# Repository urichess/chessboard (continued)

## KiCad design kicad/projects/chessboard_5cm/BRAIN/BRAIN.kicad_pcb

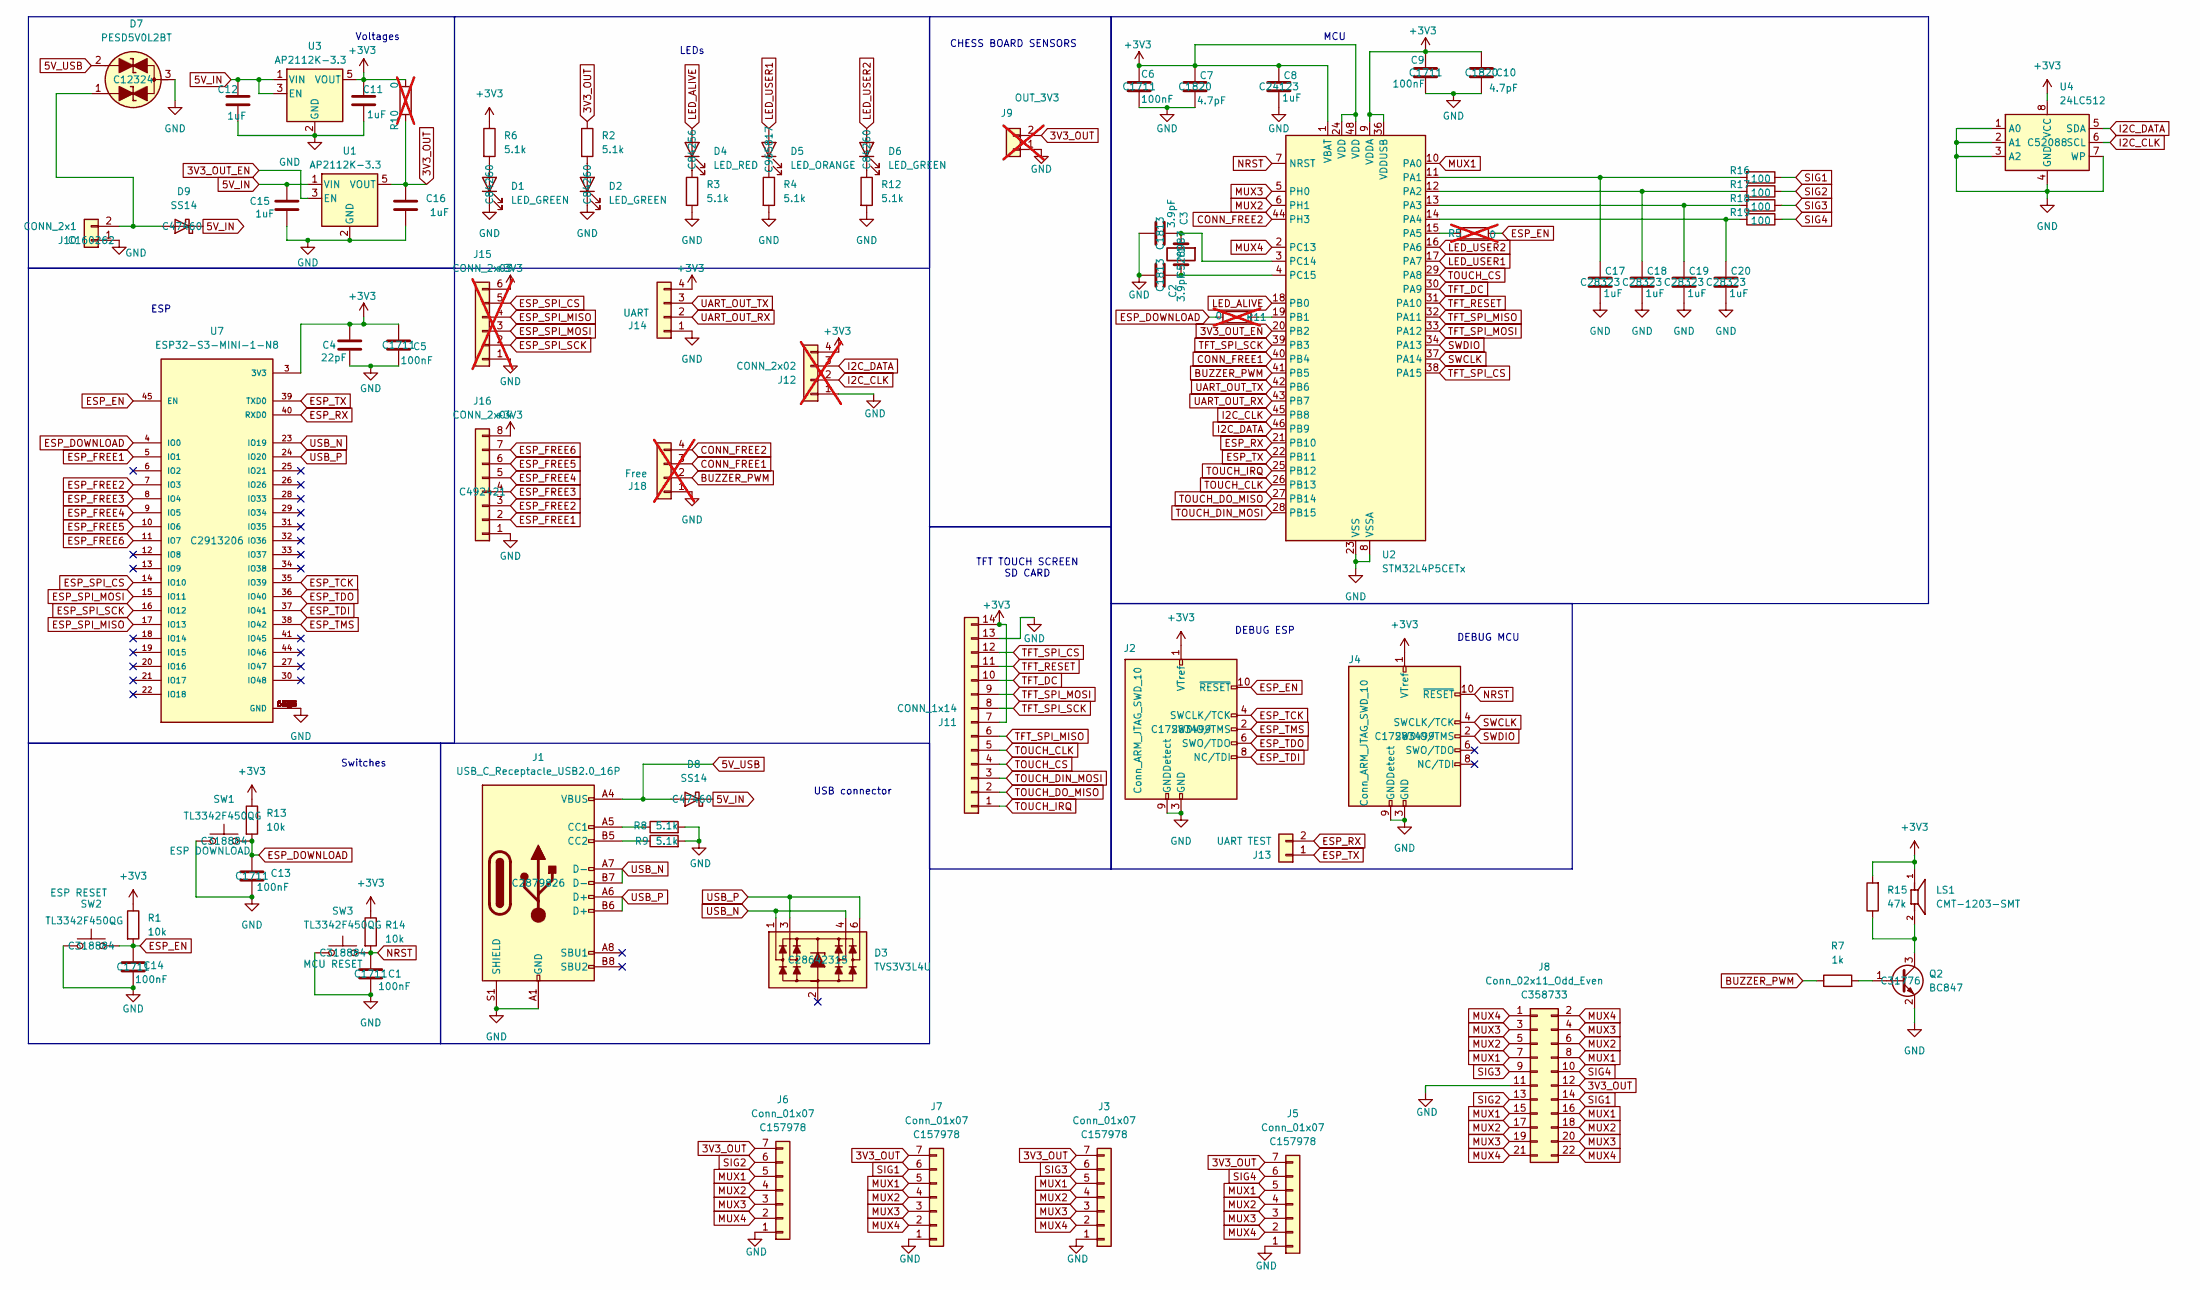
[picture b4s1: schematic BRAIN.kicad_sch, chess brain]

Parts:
C1, C5, C6, C9, C13, C14: 100nF; C_0805_2012Metric_Pad1.18x1.45mm_HandSolder; LCSC p/n C1711
C2, C3: 3.9pF; C_0805_2012Metric_Pad1.18x1.45mm_HandSolder; LCSC p/n C1813
C4: 22pF; C_0805_2012Metric_Pad1.18x1.45mm_HandSolder; LCSC p/n C1804
C7, C10: 4.7pF; C_0805_2012Metric_Pad1.18x1.45mm_HandSolder; LCSC p/n C1820
C8, C11, C12, C15, C16: 1uF; C_0805_2012Metric_Pad1.18x1.45mm_HandSolder; LCSC p/n C24123
C17, C18, C19, C20: 1uF; C_0805_2012Metric_Pad1.18x1.45mm_HandSolder; LCSC p/n C28323
D1, D2, D6: LED_GREEN; LED_0805_2012Metric_Pad1.15x1.40mm_HandSolder; LCSC p/n C84260
D3: TVS3V3L4U; TSOP-6_1.65x3.05mm_P0.95mm; LCSC p/n C28642315
D4: LED_RED; LED_0805_2012Metric_Pad1.15x1.40mm_HandSolder; LCSC p/n C84256
D5: LED_ORANGE; LED_0805_2012Metric_Pad1.15x1.40mm_HandSolder; LCSC p/n C965817
D7: PESD5V0L2BT; SOT-23; LCSC p/n C12324
D8, D9: SS14; D_SMA; LCSC p/n C47460
J1: USB_C_Receptacle_USB2.0_16P; USB_C_Receptacle_GCT_USB4105-xx-A_16P_TopMnt_Horizontal_Mod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; LCSC p/n C2879826
J2, J4: Conn_ARM_JTAG_SWD_10; GCT_BD125-10-A-0305-0580-L-B; LCSC p/n C17283499
J3, J5, J6, J7: Conn_01x07; JST_B7B-ZR_LF__SN_; LCSC p/n C157978
J8: Conn_02x11_Odd_Even; PinSocket_2x11_P2.54mm_Vertical; LCSC p/n C358733
J9: CONN_01x02; PinSocket_1x02_P2.54mm_Vertical; LCSC p/n C2935896; not fitted
J10: CONN_2x1; JST_EH_B2B-EH-A_1x02_P2.50mm_Vertical; LCSC p/n C160262
J11: CONN_1x14; PinSocket_1x14_P2.54mm_Vertical; LCSC p/n C2883731
J12: CONN_2x02; PinHeader_2x02_P2.54mm_Vertical; LCSC p/n C160338; not fitted
J13: UART TEST; PinHeader_1x02_P2.54mm_Vertical; LCSC p/n C234182
J14: UART; PinHeader_1x04_P2.54mm_Vertical; LCSC p/n C2691448
J15: CONN_2x03; PinHeader_2x03_P2.54mm_Vertical; LCSC p/n C492421; not fitted
J16: CONN_2x04; PinHeader_2x04_P2.54mm_Vertical; LCSC p/n C492421
J18: Free; PinHeader_1x04_P2.54mm_Vertical; LCSC p/n C2691448; not fitted
LS1: CMT-1203-SMT; CUI_CMT-1203-SMT; PARTREV 1.01
Q2: BC847; SOT-23; LCSC p/n C31776
R1, R13, R14: 10k; R_0805_2012Metric_Pad1.20x1.40mm_HandSolder; LCSC p/n C84376
R2, R3, R4, R6, R8, R9, R12: 5.1k; R_0805_2012Metric_Pad1.20x1.40mm_HandSolder; LCSC p/n C84375
R5, R10, R11: 0; R_0805_2012Metric_Pad1.20x1.40mm_HandSolder; not fitted
R7: 1k; R_0805_2012Metric_Pad1.20x1.40mm_HandSolder; LCSC p/n C95781
R15: 47k; R_0805_2012Metric_Pad1.20x1.40mm_HandSolder; LCSC p/n C126351
R16, R17, R18, R19: 100; R_0805_2012Metric_Pad1.20x1.40mm_HandSolder; LCSC p/n C17408
SW1, SW2, SW3: TL3342F450QG; SW_SPST_TL3342; LCSC p/n C318884
U1, U3: AP2112K-3.3; SOT-23-5; LCSC p/n C23380830
U2: STM32L4P5CETx; LQFP-48_7x7mm_P0.5mm; LCSC p/n C3227057
U4: 24LC512; SOIC-8_3.9x4.9mm_P1.27mm; LCSC p/n C52088
U7: ESP32-S3-MINI-1-N8; XCVR_ESP32-S3-MINI-1-N8; PARTREV v0.6; LCSC p/n C2913206
Y1: NX3215SA-32.768KHZ-EXS00A-MU00525; Crystal_SMD_MicroCrystal_CC7V-T1A-2Pin_3.2x1.5mm_HandSolder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; LCSC p/n C528987

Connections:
3V3_OUT: C16.1, J3.7, J5.7, J6.7, J7.7, J8.12, J9.2, R2.1, R10.1, U1.5 (VOUT)
3V3_OUT_EN: U1.3 (EN), U2.20 (PB2)
5V_IN: C12.1, C15.1, D8.1 (K), D9.1 (K), U1.1 (VIN), U3.1 (VIN), U3.3 (EN)
5V_USB: D7.2 (A2), D8.2 (A), J1.A4 (VBUS), J1.A9 (VBUS), J1.B4 (VBUS), J1.B9 (VBUS)
+3V3: C4.1, C5.1, C6.1, C7.1, C8.1, C9.1, C10.1, C11.1, J2.1 (VTref), J4.1 (VTref), J11.7, J11.14, J12.4, J14.4, J15.6, J16.8, LS1.1, R1.1, R6.1, R10.2, R13.1, R14.1, R15.2, U2.1 (VBAT), U2.9 (VDDA), U2.24 (VDD), U2.36 (VDDUSB), U2.48 (VDD), U3.5 (VOUT), U4.8 (VCC), U7.3 (3V3)
BUZZER_PWM: J18.2, R7.1, U2.41 (PB5)
CONN_FREE1: J18.3, U2.40 (PB4)
CONN_FREE2: J18.4, U2.44 (PH3)
ESP_DOWNLOAD: C13.1, R11.2, R13.2, SW1.2, U7.4 (IO0)
ESP_EN: C14.1, J2.10 (~RESET), R1.2, R5.2, SW2.2, U7.45 (EN)
ESP_FREE1: J16.2, U7.5 (IO1)
ESP_FREE2: J16.3, U7.7 (IO3)
ESP_FREE3: J16.4, U7.8 (IO4)
ESP_FREE4: J16.5, U7.9 (IO5)
ESP_FREE5: J16.6, U7.10 (IO6)
ESP_FREE6: J16.7, U7.11 (IO7)
ESP_RX: J13.2, U2.21 (PB10), U7.40 (RXD0)
ESP_SPI_CS: J15.5, U7.14 (IO10)
ESP_SPI_MISO: J15.4, U7.17 (IO13)
ESP_SPI_MOSI: J15.3, U7.15 (IO11)
ESP_SPI_SCK: J15.2, U7.16 (IO12)
ESP_TCK: J2.4 (SWCLK/TCK), U7.35 (IO39)
ESP_TDI: J2.8 (NC/TDI), U7.37 (IO41)
ESP_TDO: J2.6 (SWO/TDO), U7.36 (IO40)
ESP_TMS: J2.2 (SWDIO/TMS), U7.38 (IO42)
ESP_TX: J13.1, U2.22 (PB11), U7.39 (TXD0)
GND: C1.1, C2.2, C3.2, C4.2, C5.2, C6.2, C7.2, C8.2, C9.2, C10.2, C11.2, C12.2, C13.2, C14.2, C15.2, C16.2, C17.2, C18.2, C19.2, C20.2, D1.1 (K), D2.1 (K), D7.3 (Com), J1.A1 (GND), J1.A12 (GND), J1.B1 (GND), J1.B12 (GND), J1.S1 (SHIELD), J2.3 (GND), J2.5 (GND), J2.9 (GNDDetect), J3.1, J4.3 (GND), J4.5 (GND), J4.9 (GNDDetect), J5.1, J6.1, J7.1, J8.11, J9.1, J10.1, J11.13, J12.1, J14.1, J15.1, J16.1, J18.1, Q2.2 (E), R3.2, R4.2, R8.2, R9.2, R12.2, SW1.1, SW2.1, SW3.1, U1.2 (GND), U2.8 (VSSA), U2.23 (VSS), U2.35 (VSS), U2.47 (VSS), U3.2 (GND), U4.1 (A0), U4.2 (A1), U4.3 (A2), U4.4 (GND), U4.7 (WP), U7.1 (GND), U7.2 (GND), U7.42 (GND), U7.43 (GND), U7.46 (GND), U7.47 (GND), U7.48 (GND), U7.49 (GND), U7.50 (GND), U7.51 (GND), U7.52 (GND), U7.53 (GND), U7.54 (GND), U7.55 (GND), U7.56 (GND), U7.57 (GND), U7.58 (GND), U7.59 (GND), U7.60 (GND), U7.61 (GND), U7.61_1 (GND), U7.61_2 (GND), U7.61_3 (GND), U7.61_4 (GND), U7.61_5 (GND), U7.61_6 (GND), U7.61_7 (GND), U7.61_8 (GND), U7.62 (GND), U7.63 (GND), U7.64 (GND), U7.65 (GND)
I2C_CLK: J12.2, U2.45 (PB8), U4.6 (SCL)
I2C_DATA: J12.3, U2.46 (PB9), U4.5 (SDA)
LED_ALIVE: D4.2 (A), U2.18 (PB0)
LED_USER1: D5.2 (A), U2.17 (PA7)
LED_USER2: D6.2 (A), U2.16 (PA6)
MUX1: J3.5, J5.5, J6.5, J7.5, J8.7, J8.8, J8.15, J8.16, U2.10 (PA0)
MUX2: J3.4, J5.4, J6.4, J7.4, J8.5, J8.6, J8.17, J8.18, U2.6 (PH1)
MUX3: J3.3, J5.3, J6.3, J7.3, J8.3, J8.4, J8.19, J8.20, U2.5 (PH0)
MUX4: J3.2, J5.2, J6.2, J7.2, J8.1, J8.2, J8.21, J8.22, U2.2 (PC13)
NRST: C1.2, J4.10 (~RESET), R14.2, SW3.2, U2.7 (NRST)
unnamed: D1.2 (A), R6.2
unnamed: D2.2 (A), R2.2
unnamed: D4.1 (K), R3.1
unnamed: D5.1 (K), R4.1
unnamed: D6.1 (K), R12.1
unnamed: D7.1 (A1), D9.2 (A), J10.2
unnamed: J1.A5 (CC1), R8.1
unnamed: J1.B5 (CC2), R9.1
unnamed: Q2.1 (B), R7.2
unnamed: LS1.2, Q2.3 (C), R15.1
unnamed: C17.1, R16.2, U2.11 (PA1)
unnamed: C18.1, R17.2, U2.12 (PA2)
unnamed: C19.1, R18.2, U2.13 (PA3)
unnamed: C20.1, R19.2, U2.14 (PA4)
unnamed: R5.1, U2.15 (PA5)
unnamed: R11.1, U2.19 (PB1)
unnamed: C3.1, U2.3 (PC14), Y1.1
unnamed: C2.1, U2.4 (PC15), Y1.2
SIG1: J7.6, J8.14, R16.1
SIG2: J6.6, J8.13, R17.1
SIG3: J3.6, J8.9, R18.1
SIG4: J5.6, J8.10, R19.1
SWCLK: J4.4 (SWCLK/TCK), U2.37 (PA14)
SWDIO: J4.2 (SWDIO/TMS), U2.34 (PA13)
TFT_DC: J11.10, U2.30 (PA9)
TFT_RESET: J11.11, U2.31 (PA10)
TFT_SPI_CS: J11.12, U2.38 (PA15)
TFT_SPI_MISO: J11.6, U2.32 (PA11)
TFT_SPI_MOSI: J11.9, U2.33 (PA12)
TFT_SPI_SCK: J11.8, U2.39 (PB3)
TOUCH_CLK: J11.5, U2.26 (PB13)
TOUCH_CS: J11.4, U2.29 (PA8)
TOUCH_DIN_MOSI: J11.3, U2.28 (PB15)
TOUCH_DO_MISO: J11.2, U2.27 (PB14)
TOUCH_IRQ: J11.1, U2.25 (PB12)
UART_OUT_RX: J14.2, U2.43 (PB7)
UART_OUT_TX: J14.3, U2.42 (PB6)
USB_N: D3.1 (L1), D3.4 (L3), J1.A7 (D-), J1.B7 (D-), U7.23 (IO19)
USB_P: D3.3 (L2), D3.6 (L4), J1.A6 (D+), J1.B6 (D+), U7.24 (IO20)

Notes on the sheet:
MCU
LEDs
DEBUG MCU
CHESS BOARD SENSORS
TFT TOUCH SCREEN SD CARD
ESP
Switches
USB connector
Voltages
DEBUG ESP

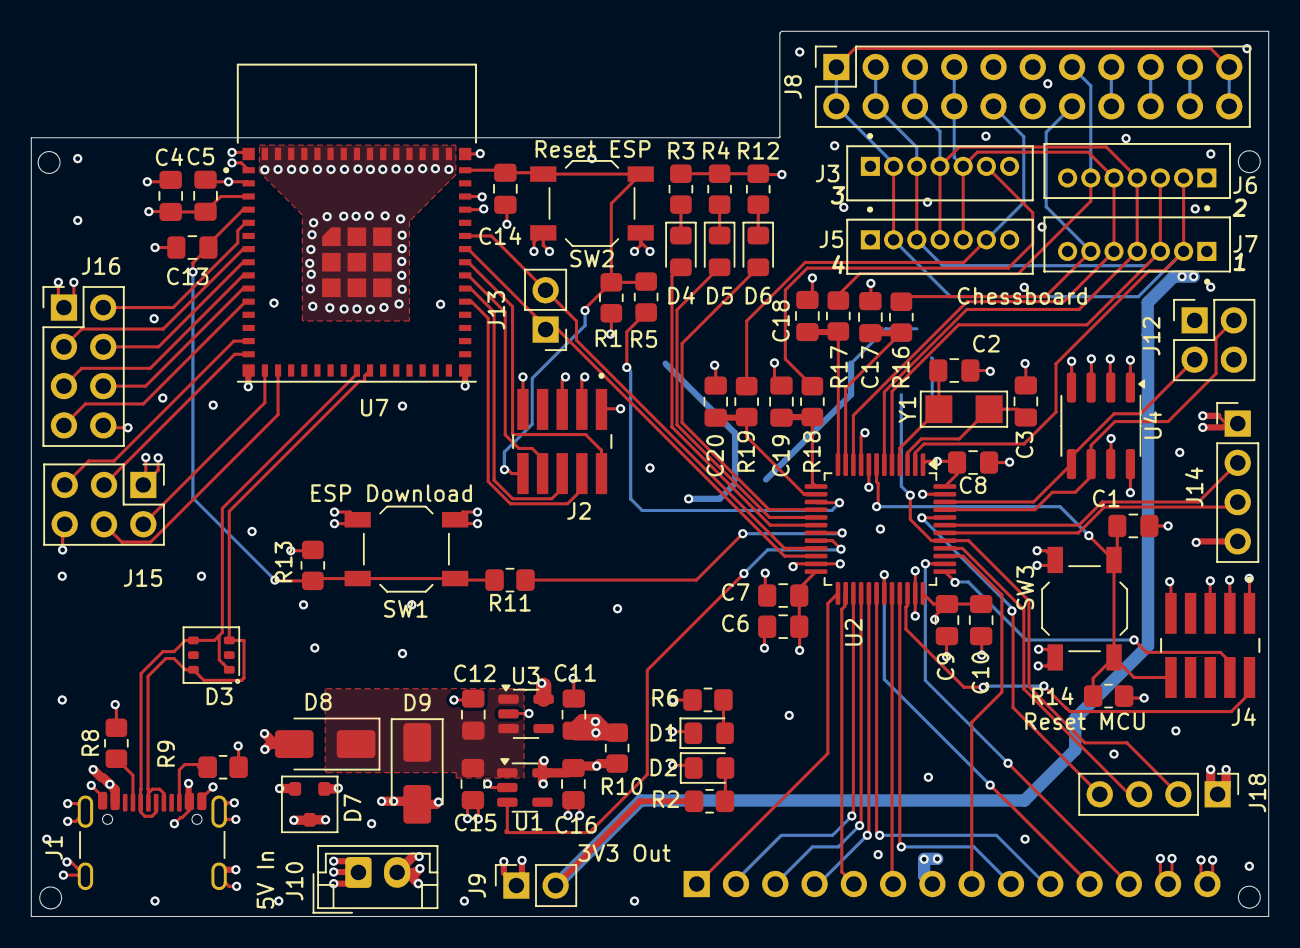
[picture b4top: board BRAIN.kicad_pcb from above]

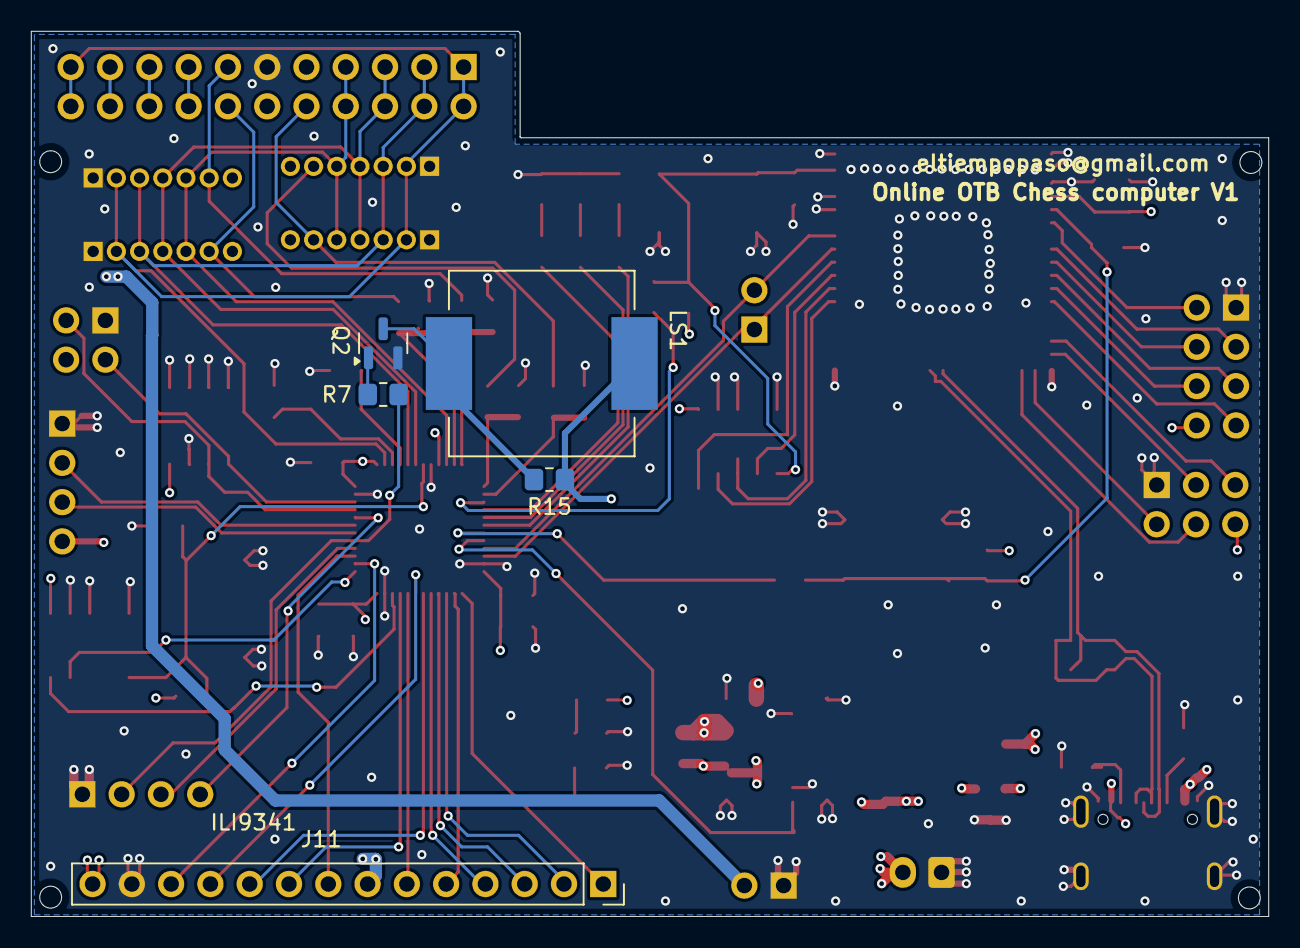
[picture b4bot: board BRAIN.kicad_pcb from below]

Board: 4 copper layers, 80.0 x 57.2 mm, 76 parts (5 on the bottom side), 76 nets.

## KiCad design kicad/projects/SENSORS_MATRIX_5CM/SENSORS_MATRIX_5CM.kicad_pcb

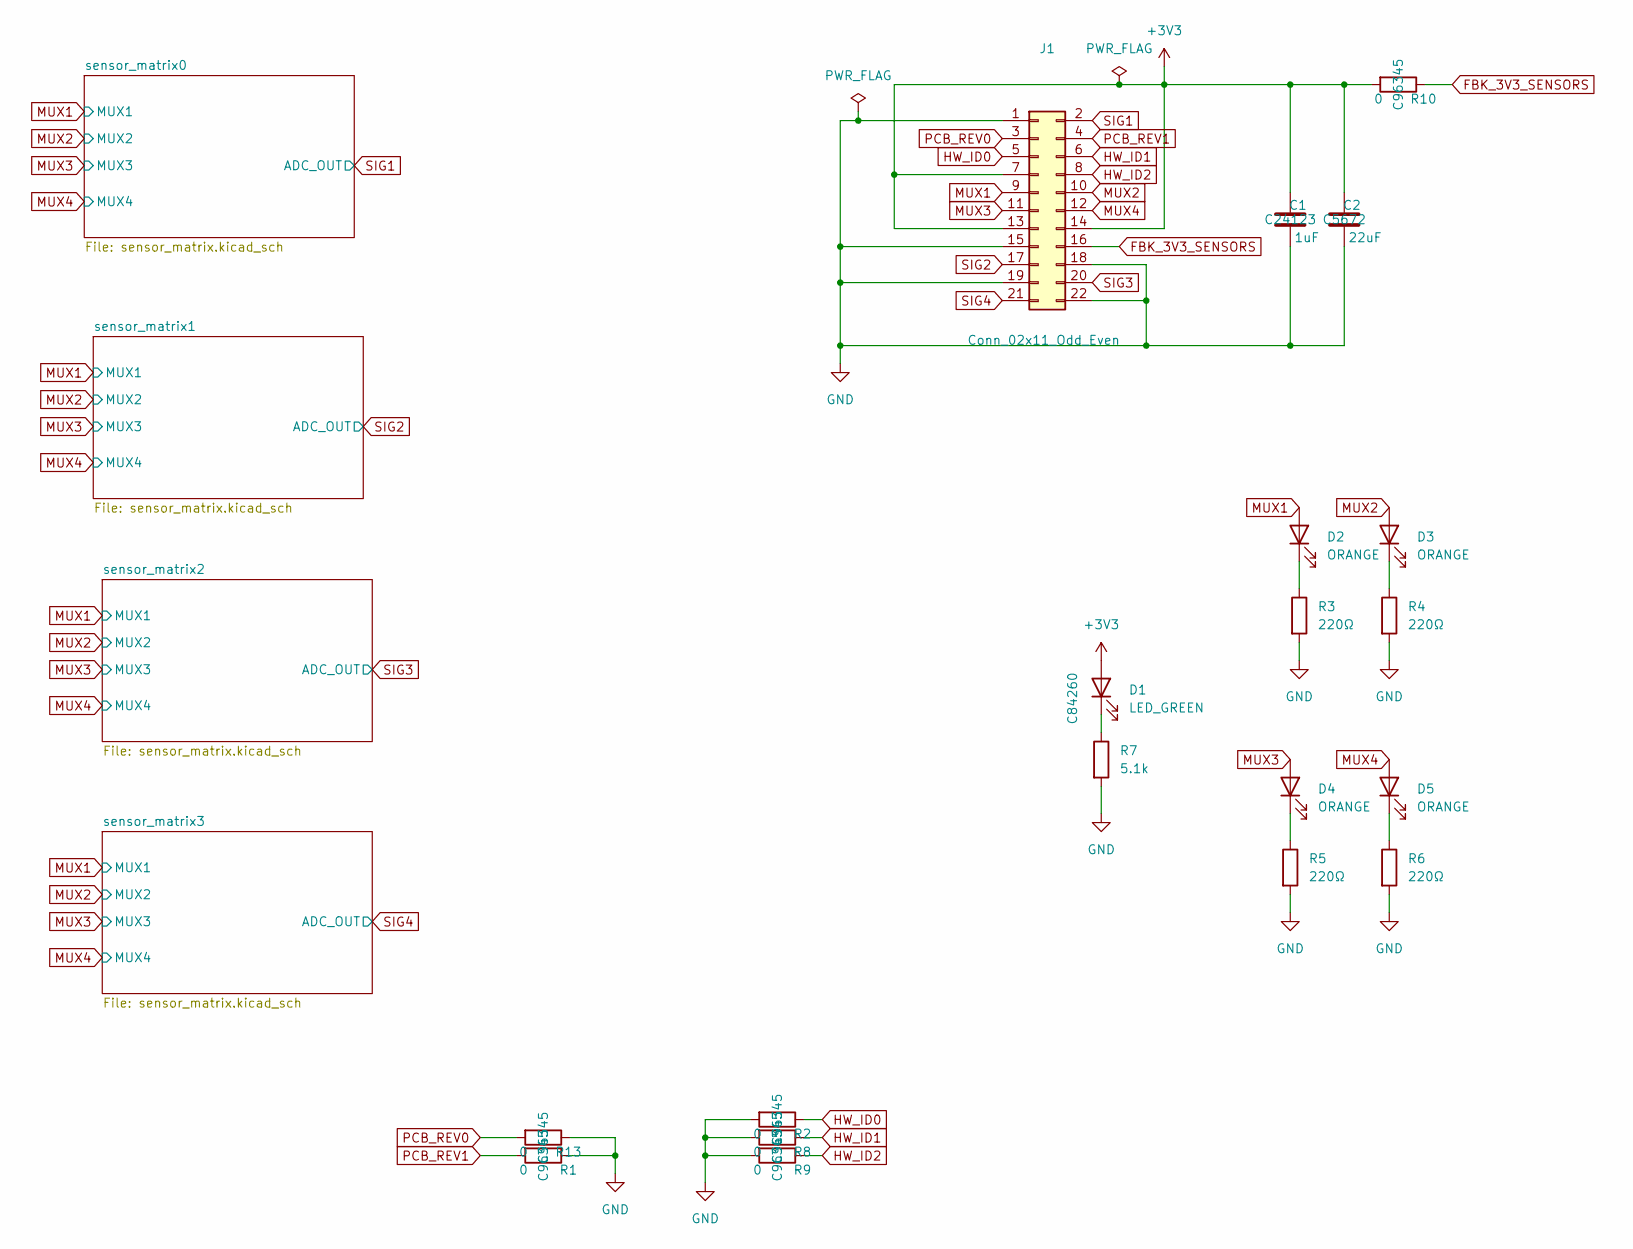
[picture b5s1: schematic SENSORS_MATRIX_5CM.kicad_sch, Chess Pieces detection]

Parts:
C1: 1uF; C_0805_2012Metric_Pad1.18x1.45mm_HandSolder; LCSC p/n C24123
C2: 22uF; C_1206_3216Metric_Pad1.33x1.80mm_HandSolder; LCSC p/n C5672
D1: LED_GREEN; LED_0805_2012Metric_Pad1.15x1.40mm_HandSolder; LCSC p/n C84260
D2, D3, D4, D5: ORANGE; LED_0805_2012Metric_Pad1.15x1.40mm_HandSolder; LCSC p/n C434437
J1: Conn_02x11_Odd_Even; PinSocket_2x11_P2.54mm_Horizontal
R1, R2, R8, R9, R10, R13: 0; R_0805_2012Metric_Pad1.20x1.40mm_HandSolder; LCSC p/n C96345
R3, R4, R5, R6: 220Ω; R_0805_2012Metric_Pad1.20x1.40mm_HandSolder; LCSC p/n C114519
R7: 5.1k; R_0805_2012Metric_Pad1.20x1.40mm_HandSolder; LCSC p/n C84375

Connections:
+3V3: C1.1, C2.1, D1.2 (A), J1.7, J1.13, J1.14, R10.2; also elsewhere on the board
FBK_3V3_SENSORS: J1.16, R10.1
GND: C1.2, C2.2, J1.1, J1.15, J1.18, J1.19, J1.22, R1.1, R2.2, R3.2, R4.2, R5.2, R6.2, R7.2, R8.2, R9.2, R13.1; also elsewhere on the board
HW_ID0: J1.5, R2.1
HW_ID1: J1.6, R8.1
HW_ID2: J1.8, R9.1
MUX1: D2.2 (A), J1.9; also elsewhere on the board
MUX2: D3.2 (A), J1.10; also elsewhere on the board
MUX3: D4.2 (A), J1.11; also elsewhere on the board
MUX4: D5.2 (A), J1.12; also elsewhere on the board
unnamed: D1.1 (K), R7.1
unnamed: D2.1 (K), R3.1
unnamed: D3.1 (K), R4.1
unnamed: D4.1 (K), R5.1
unnamed: D5.1 (K), R6.1
PCB_REV0: J1.3, R13.2
PCB_REV1: J1.4, R1.2
SIG1: J1.2; also elsewhere on the board
SIG2: J1.17; also elsewhere on the board
SIG3: J1.20; also elsewhere on the board
SIG4: J1.21; also elsewhere on the board

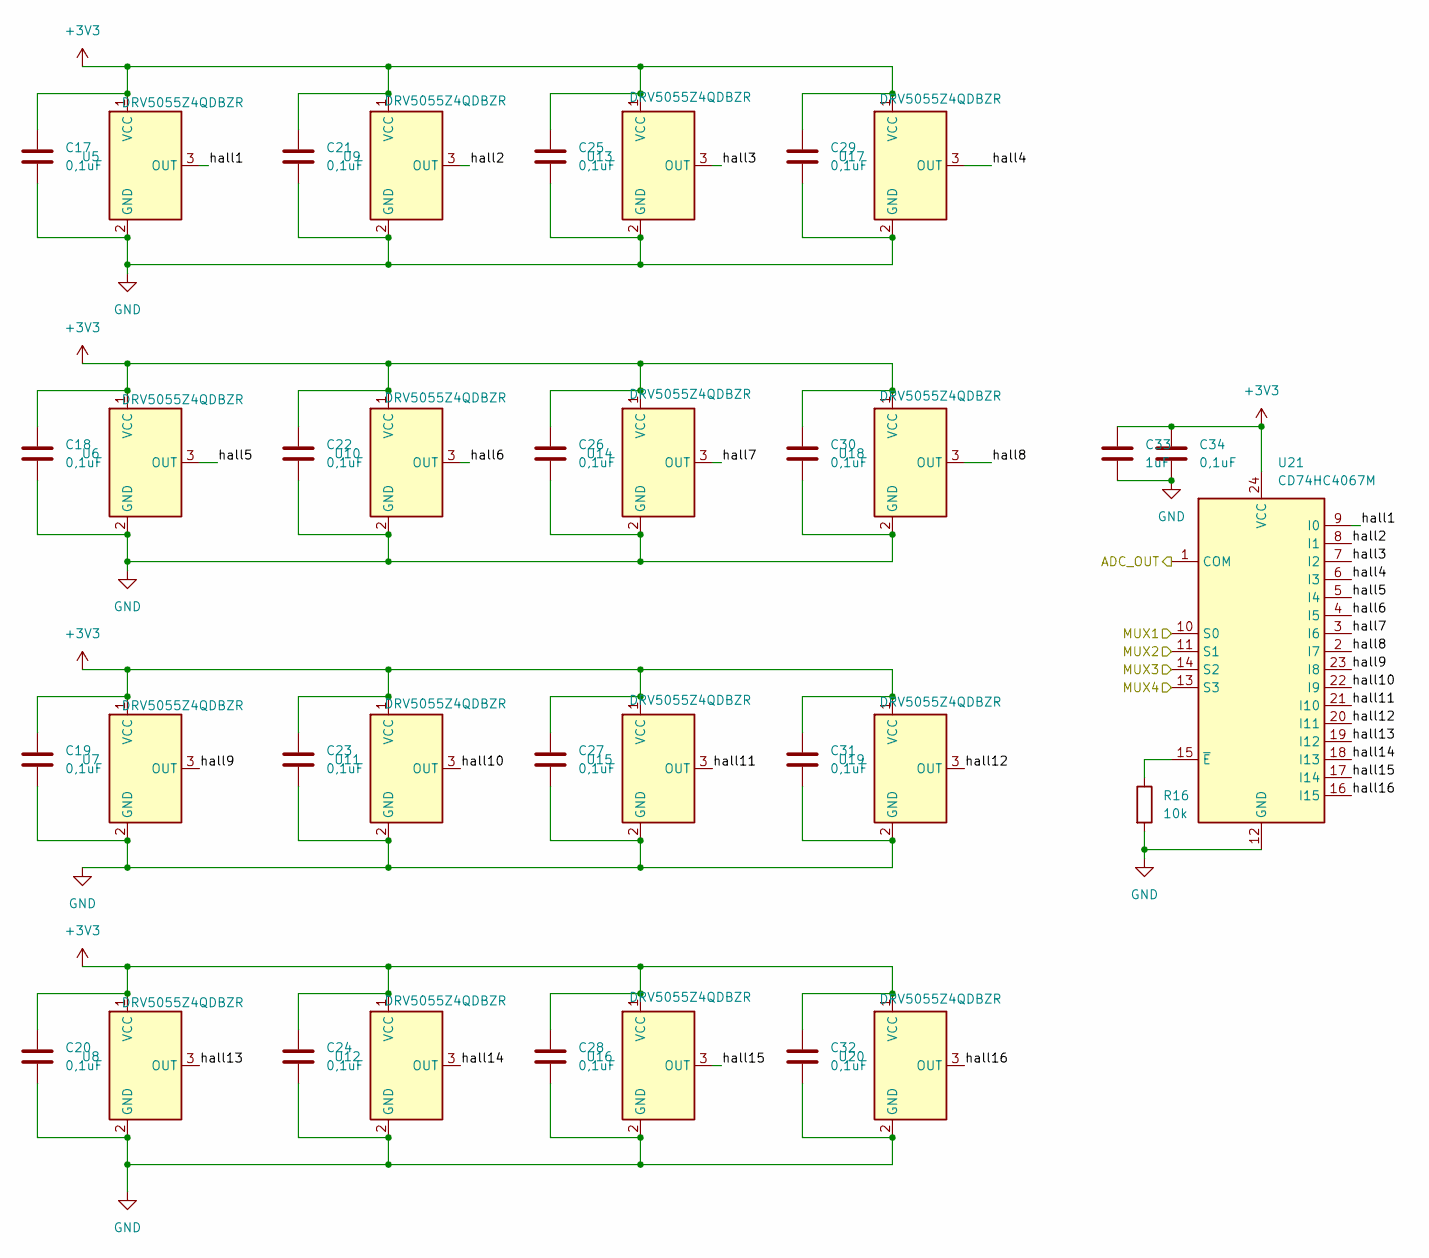
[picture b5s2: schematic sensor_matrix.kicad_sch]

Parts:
C17, C18, C19, C20, C21, C22, C23, C24, C25, C26, C27, C28, C29, C30, C31, C32, C34: 0,1uF; C_0805_2012Metric_Pad1.18x1.45mm_HandSolder; LCSC p/n C1711
C33: 1uF; C_0805_2012Metric_Pad1.18x1.45mm_HandSolder; LCSC p/n C24123
R16: 10k; R_0805_2012Metric_Pad1.20x1.40mm_HandSolder; LCSC p/n C84376
U5, U6, U7, U8, U9, U10, U11, U12, U13, U14, U15, U16, U17, U18, U19, U20: DRV5055Z4QDBZR; SOT-23_Handsoldering; LCSC p/n C2864477
U21: CD74HC4067M; SOIC-24W_7.5x15.4mm_P1.27mm; LCSC p/n C496123

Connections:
+3V3: C17.1, C18.1, C19.1, C20.1, C21.1, C22.1, C23.1, C24.1, C25.1, C26.1, C27.1, C28.1, C29.1, C30.1, C31.1, C32.1, C33.1, C34.1, U5.1 (VCC), U6.1 (VCC), U7.1 (VCC), U8.1 (VCC), U9.1 (VCC), U10.1 (VCC), U11.1 (VCC), U12.1 (VCC), U13.1 (VCC), U14.1 (VCC), U15.1 (VCC), U16.1 (VCC), U17.1 (VCC), U18.1 (VCC), U19.1 (VCC), U20.1 (VCC), U21.24 (VCC); also elsewhere on the board
/sensor_matrix0/hall1: U5.3 (OUT), U21.9 (I0)
/sensor_matrix0/hall2: U9.3 (OUT), U21.8 (I1)
/sensor_matrix0/hall3: U13.3 (OUT), U21.7 (I2)
/sensor_matrix0/hall4: U17.3 (OUT), U21.6 (I3)
/sensor_matrix0/hall5: U6.3 (OUT), U21.5 (I4)
/sensor_matrix0/hall6: U10.3 (OUT), U21.4 (I5)
/sensor_matrix0/hall7: U14.3 (OUT), U21.3 (I6)
/sensor_matrix0/hall8: U18.3 (OUT), U21.2 (I7)
/sensor_matrix0/hall9: U7.3 (OUT), U21.23 (I8)
/sensor_matrix0/hall10: U11.3 (OUT), U21.22 (I9)
/sensor_matrix0/hall11: U15.3 (OUT), U21.21 (I10)
/sensor_matrix0/hall12: U19.3 (OUT), U21.20 (I11)
/sensor_matrix0/hall13: U8.3 (OUT), U21.19 (I12)
/sensor_matrix0/hall14: U12.3 (OUT), U21.18 (I13)
/sensor_matrix0/hall15: U16.3 (OUT), U21.17 (I14)
/sensor_matrix0/hall16: U20.3 (OUT), U21.16 (I15)
GND: C17.2, C18.2, C19.2, C20.2, C21.2, C22.2, C23.2, C24.2, C25.2, C26.2, C27.2, C28.2, C29.2, C30.2, C31.2, C32.2, C33.2, C34.2, R16.2, U5.2 (GND), U6.2 (GND), U7.2 (GND), U8.2 (GND), U9.2 (GND), U10.2 (GND), U11.2 (GND), U12.2 (GND), U13.2 (GND), U14.2 (GND), U15.2 (GND), U16.2 (GND), U17.2 (GND), U18.2 (GND), U19.2 (GND), U20.2 (GND), U21.12 (GND); also elsewhere on the board
MUX1: U21.10 (S0); also elsewhere on the board
MUX2: U21.11 (S1); also elsewhere on the board
MUX3: U21.14 (S2); also elsewhere on the board
MUX4: U21.13 (S3); also elsewhere on the board
unnamed: R16.1, U21.15 (~E)
SIG1: U21.1 (COM); also elsewhere on the board

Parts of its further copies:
C35, C36, C37, C38, C39, C40, C41, C42, C43, C44, C45, C46, C47, C48, C49, C50, C52, C53, C54, C55, C56, C57, C58, C59, C60, C61, C62, C63, C64, C65, C66, C67, C68, C70, C71, C72, C73, C74, C75, C76, C77, C78, C79, C80, C81, C82, C83, C84, C85, C86, C88: 0,1uF; C_0805_2012Metric_Pad1.18x1.45mm_HandSolder; LCSC p/n C1711
C51, C69, C87: 1uF; C_0805_2012Metric_Pad1.18x1.45mm_HandSolder; LCSC p/n C24123
R17, R18, R19: 10k; R_0805_2012Metric_Pad1.20x1.40mm_HandSolder; LCSC p/n C84376
U22, U23, U24, U25, U26, U27, U28, U29, U30, U31, U32, U33, U34, U35, U36, U37, U39, U40, U41, U42, U43, U44, U45, U46, U47, U48, U49, U50, U51, U52, U53, U54, U56, U57, U58, U59, U60, U61, U62, U63, U64, U65, U66, U67, U68, U69, U70, U71: DRV5055Z4QDBZR; SOT-23_Handsoldering; LCSC p/n C2864477
U38, U55, U72: CD74HC4067M; SOIC-24W_7.5x15.4mm_P1.27mm; LCSC p/n C496123

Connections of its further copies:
+3V3: C35.1, C36.1, C37.1, C38.1, C39.1, C40.1, C41.1, C42.1, C43.1, C44.1, C45.1, C46.1, C47.1, C48.1, C49.1, C50.1, C51.1, C52.1, C53.1, C54.1, C55.1, C56.1, C57.1, C58.1, C59.1, C60.1, C61.1, C62.1, C63.1, C64.1, C65.1, C66.1, C67.1, C68.1, C69.1, C70.1, C71.1, C72.1, C73.1, C74.1, C75.1, C76.1, C77.1, C78.1, C79.1, C80.1, C81.1, C82.1, C83.1, C84.1, C85.1, C86.1, C87.1, C88.1, U22.1 (VCC), U23.1 (VCC), U24.1 (VCC), U25.1 (VCC), U26.1 (VCC), U27.1 (VCC), U28.1 (VCC), U29.1 (VCC), U30.1 (VCC), U31.1 (VCC), U32.1 (VCC), U33.1 (VCC), U34.1 (VCC), U35.1 (VCC), U36.1 (VCC), U37.1 (VCC), U38.24 (VCC), U39.1 (VCC), U40.1 (VCC), U41.1 (VCC), U42.1 (VCC), U43.1 (VCC), U44.1 (VCC), U45.1 (VCC), U46.1 (VCC), U47.1 (VCC), U48.1 (VCC), U49.1 (VCC), U50.1 (VCC), U51.1 (VCC), U52.1 (VCC), U53.1 (VCC), U54.1 (VCC), U55.24 (VCC), U56.1 (VCC), U57.1 (VCC), U58.1 (VCC), U59.1 (VCC), U60.1 (VCC), U61.1 (VCC), U62.1 (VCC), U63.1 (VCC), U64.1 (VCC), U65.1 (VCC), U66.1 (VCC), U67.1 (VCC), U68.1 (VCC), U69.1 (VCC), U70.1 (VCC), U71.1 (VCC), U72.24 (VCC); also elsewhere on the board
/sensor_matrix1/hall1: U22.3 (OUT), U38.9 (I0)
/sensor_matrix1/hall2: U26.3 (OUT), U38.8 (I1)
/sensor_matrix1/hall3: U30.3 (OUT), U38.7 (I2)
/sensor_matrix1/hall4: U34.3 (OUT), U38.6 (I3)
/sensor_matrix1/hall5: U23.3 (OUT), U38.5 (I4)
/sensor_matrix1/hall6: U27.3 (OUT), U38.4 (I5)
/sensor_matrix1/hall7: U31.3 (OUT), U38.3 (I6)
/sensor_matrix1/hall8: U35.3 (OUT), U38.2 (I7)
/sensor_matrix1/hall9: U24.3 (OUT), U38.23 (I8)
/sensor_matrix1/hall10: U28.3 (OUT), U38.22 (I9)
/sensor_matrix1/hall11: U32.3 (OUT), U38.21 (I10)
/sensor_matrix1/hall12: U36.3 (OUT), U38.20 (I11)
/sensor_matrix1/hall13: U25.3 (OUT), U38.19 (I12)
/sensor_matrix1/hall14: U29.3 (OUT), U38.18 (I13)
/sensor_matrix1/hall15: U33.3 (OUT), U38.17 (I14)
/sensor_matrix1/hall16: U37.3 (OUT), U38.16 (I15)
/sensor_matrix2/hall1: U39.3 (OUT), U55.9 (I0)
/sensor_matrix2/hall2: U43.3 (OUT), U55.8 (I1)
/sensor_matrix2/hall3: U47.3 (OUT), U55.7 (I2)
/sensor_matrix2/hall4: U51.3 (OUT), U55.6 (I3)
/sensor_matrix2/hall5: U40.3 (OUT), U55.5 (I4)
/sensor_matrix2/hall6: U44.3 (OUT), U55.4 (I5)
/sensor_matrix2/hall7: U48.3 (OUT), U55.3 (I6)
/sensor_matrix2/hall8: U52.3 (OUT), U55.2 (I7)
/sensor_matrix2/hall9: U41.3 (OUT), U55.23 (I8)
/sensor_matrix2/hall10: U45.3 (OUT), U55.22 (I9)
/sensor_matrix2/hall11: U49.3 (OUT), U55.21 (I10)
/sensor_matrix2/hall12: U53.3 (OUT), U55.20 (I11)
/sensor_matrix2/hall13: U42.3 (OUT), U55.19 (I12)
/sensor_matrix2/hall14: U46.3 (OUT), U55.18 (I13)
/sensor_matrix2/hall15: U50.3 (OUT), U55.17 (I14)
/sensor_matrix2/hall16: U54.3 (OUT), U55.16 (I15)
/sensor_matrix3/hall1: U56.3 (OUT), U72.9 (I0)
/sensor_matrix3/hall2: U60.3 (OUT), U72.8 (I1)
/sensor_matrix3/hall3: U64.3 (OUT), U72.7 (I2)
/sensor_matrix3/hall4: U68.3 (OUT), U72.6 (I3)
/sensor_matrix3/hall5: U57.3 (OUT), U72.5 (I4)
/sensor_matrix3/hall6: U61.3 (OUT), U72.4 (I5)
/sensor_matrix3/hall7: U65.3 (OUT), U72.3 (I6)
/sensor_matrix3/hall8: U69.3 (OUT), U72.2 (I7)
/sensor_matrix3/hall9: U58.3 (OUT), U72.23 (I8)
/sensor_matrix3/hall10: U62.3 (OUT), U72.22 (I9)
/sensor_matrix3/hall11: U66.3 (OUT), U72.21 (I10)
/sensor_matrix3/hall12: U70.3 (OUT), U72.20 (I11)
/sensor_matrix3/hall13: U59.3 (OUT), U72.19 (I12)
/sensor_matrix3/hall14: U63.3 (OUT), U72.18 (I13)
/sensor_matrix3/hall15: U67.3 (OUT), U72.17 (I14)
/sensor_matrix3/hall16: U71.3 (OUT), U72.16 (I15)
GND: C35.2, C36.2, C37.2, C38.2, C39.2, C40.2, C41.2, C42.2, C43.2, C44.2, C45.2, C46.2, C47.2, C48.2, C49.2, C50.2, C51.2, C52.2, C53.2, C54.2, C55.2, C56.2, C57.2, C58.2, C59.2, C60.2, C61.2, C62.2, C63.2, C64.2, C65.2, C66.2, C67.2, C68.2, C69.2, C70.2, C71.2, C72.2, C73.2, C74.2, C75.2, C76.2, C77.2, C78.2, C79.2, C80.2, C81.2, C82.2, C83.2, C84.2, C85.2, C86.2, C87.2, C88.2, R17.2, R18.2, R19.2, U22.2 (GND), U23.2 (GND), U24.2 (GND), U25.2 (GND), U26.2 (GND), U27.2 (GND), U28.2 (GND), U29.2 (GND), U30.2 (GND), U31.2 (GND), U32.2 (GND), U33.2 (GND), U34.2 (GND), U35.2 (GND), U36.2 (GND), U37.2 (GND), U38.12 (GND), U39.2 (GND), U40.2 (GND), U41.2 (GND), U42.2 (GND), U43.2 (GND), U44.2 (GND), U45.2 (GND), U46.2 (GND), U47.2 (GND), U48.2 (GND), U49.2 (GND), U50.2 (GND), U51.2 (GND), U52.2 (GND), U53.2 (GND), U54.2 (GND), U55.12 (GND), U56.2 (GND), U57.2 (GND), U58.2 (GND), U59.2 (GND), U60.2 (GND), U61.2 (GND), U62.2 (GND), U63.2 (GND), U64.2 (GND), U65.2 (GND), U66.2 (GND), U67.2 (GND), U68.2 (GND), U69.2 (GND), U70.2 (GND), U71.2 (GND), U72.12 (GND); also elsewhere on the board
MUX1: U38.10 (S0), U55.10 (S0), U72.10 (S0); also elsewhere on the board
MUX2: U38.11 (S1), U55.11 (S1), U72.11 (S1); also elsewhere on the board
MUX3: U38.14 (S2), U55.14 (S2), U72.14 (S2); also elsewhere on the board
MUX4: U38.13 (S3), U55.13 (S3), U72.13 (S3); also elsewhere on the board
unnamed: R17.1, U38.15 (~E)
unnamed: R18.1, U55.15 (~E)
unnamed: R19.1, U72.15 (~E)
SIG2: U38.1 (COM); also elsewhere on the board
SIG3: U55.1 (COM); also elsewhere on the board
SIG4: U72.1 (COM); also elsewhere on the board

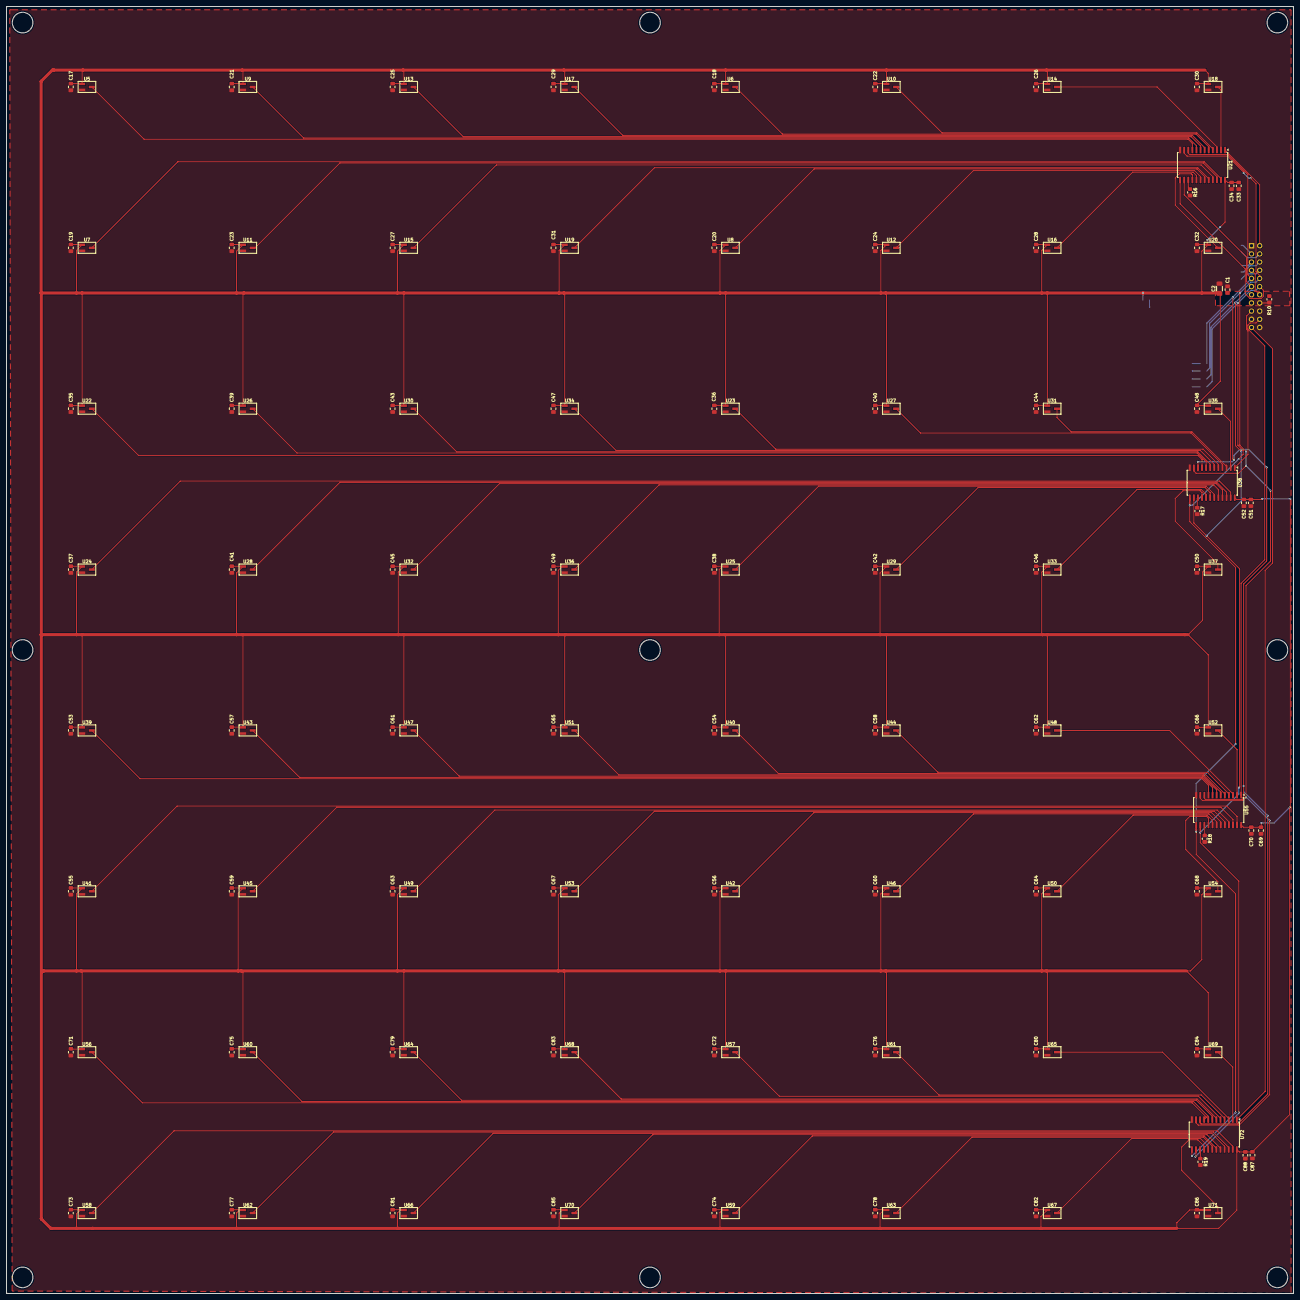
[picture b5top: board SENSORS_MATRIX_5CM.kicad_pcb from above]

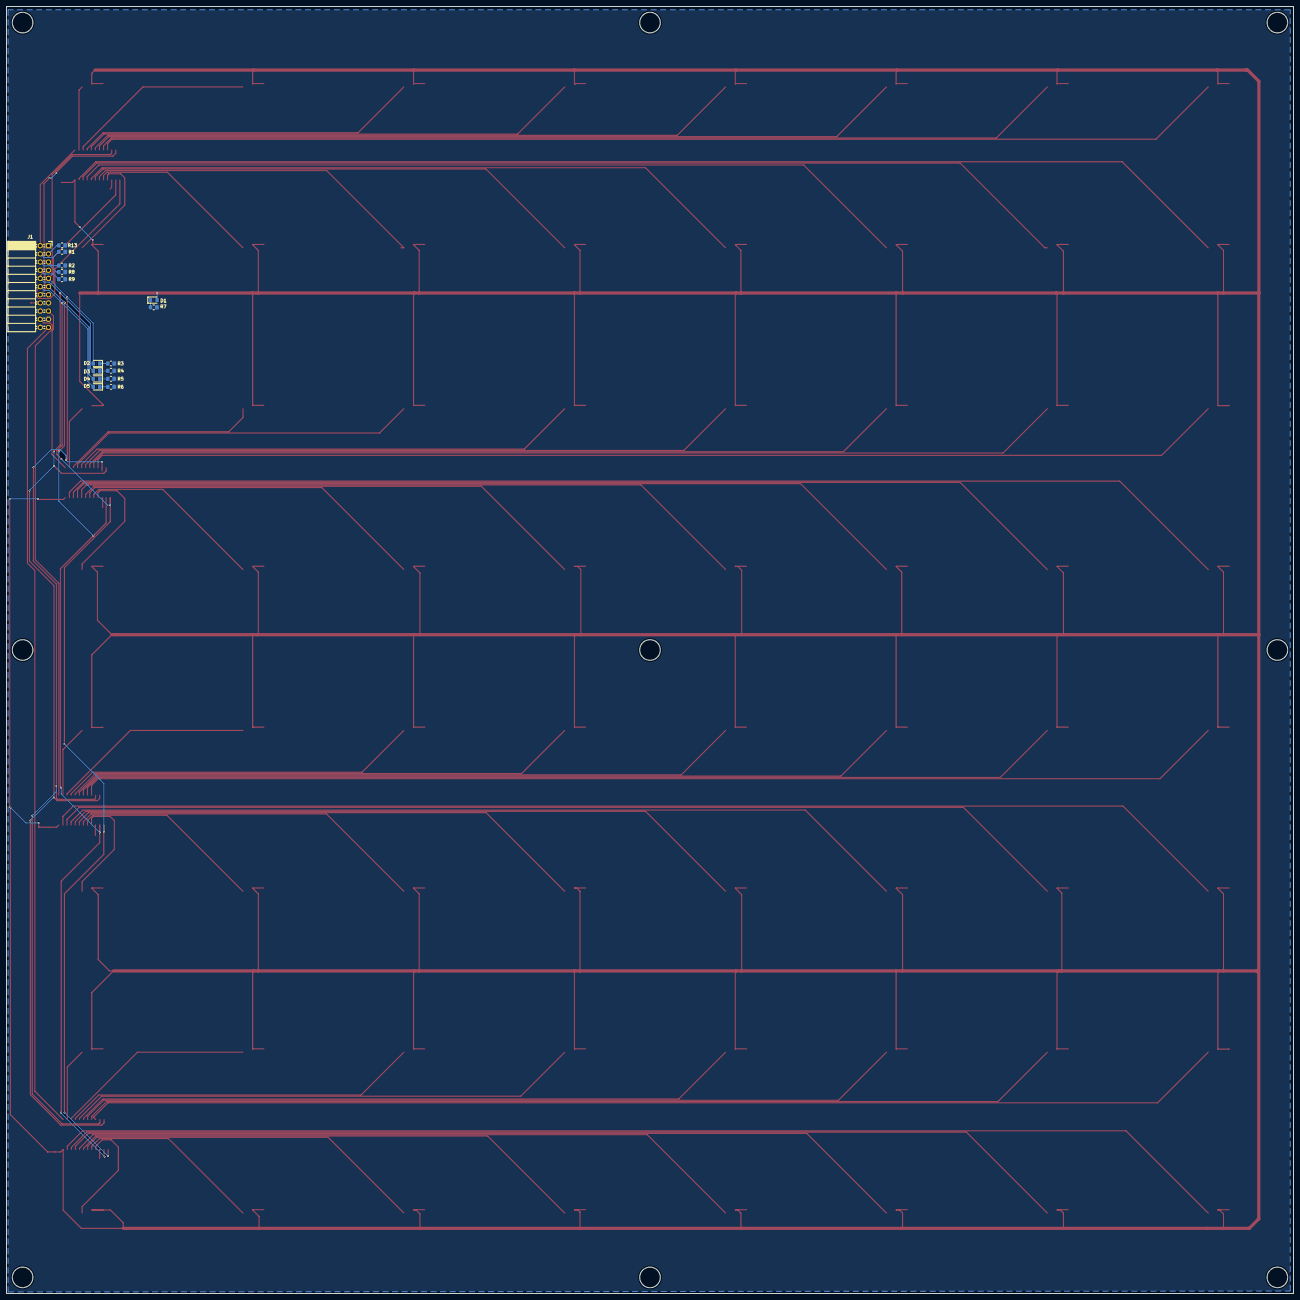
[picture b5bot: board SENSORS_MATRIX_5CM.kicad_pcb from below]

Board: 2 copper layers, 400.0 x 400.0 mm, 163 parts (16 on the bottom side), 89 nets.
